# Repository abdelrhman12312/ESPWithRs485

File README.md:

# ESPWithRs485
it's a master board that controls multiple slave ones with the esp-12e 
you can use this link to view the pcb in your browser 
https://kicanvas.org/?github=https%3A%2F%2Fgithub.com%2Fabdelrhman12312%2FESPWithRs485

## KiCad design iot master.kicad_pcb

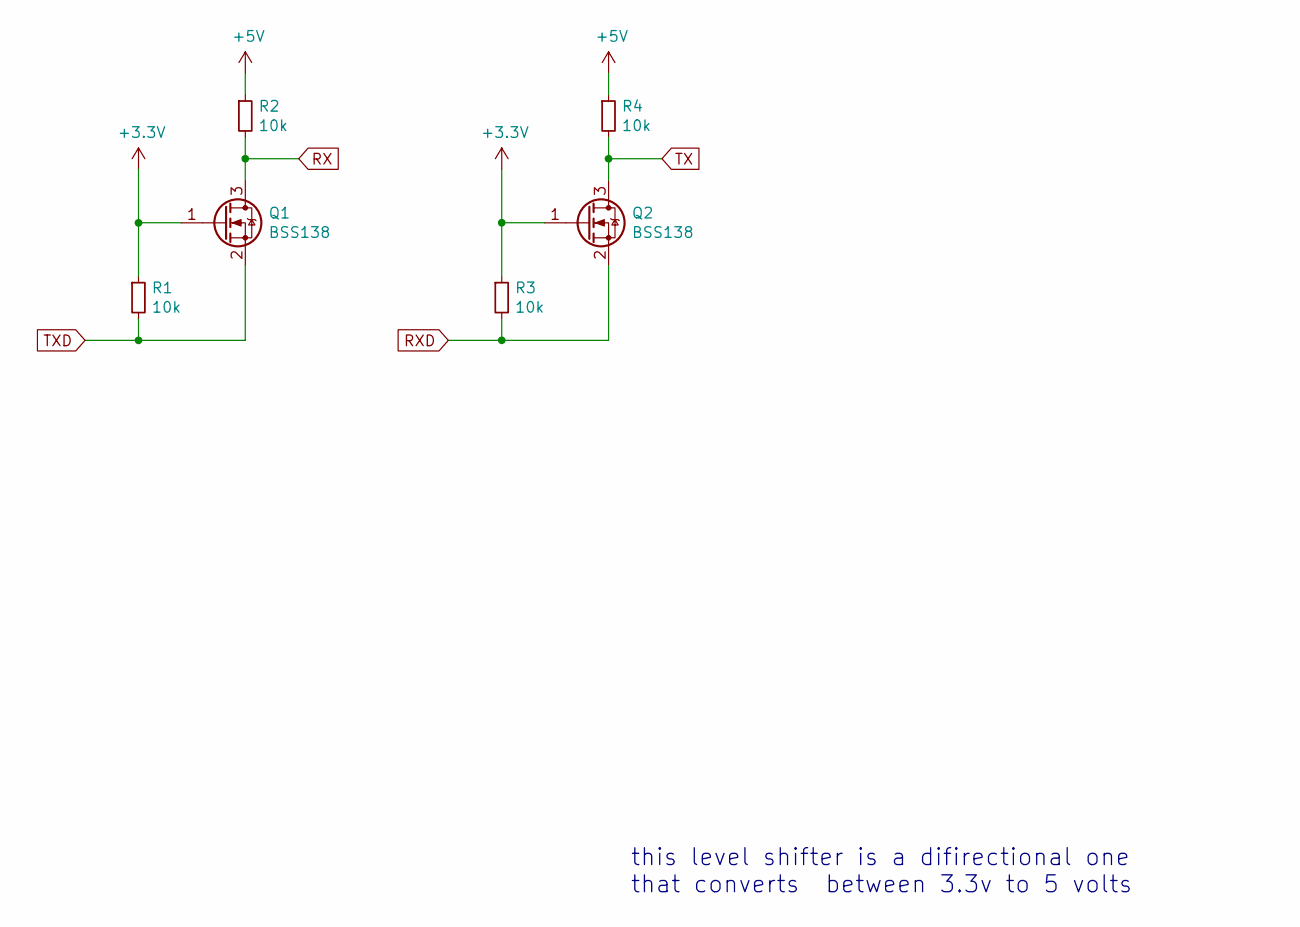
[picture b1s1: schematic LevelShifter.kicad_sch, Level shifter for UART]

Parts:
Q1, Q2: BSS138; SOT-23
R1, R2, R3, R4: 10k; R_0805_2012Metric_Pad1.15x1.40mm_HandSolder

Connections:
+3V3: Q1.1 (G), Q2.1 (G), R1.1, R3.1; also elsewhere on the board
+5V: R2.1, R4.1; also elsewhere on the board
RX: Q1.3 (D), R2.2; also elsewhere on the board
RXD: Q2.2 (S), R3.2; also elsewhere on the board
TX: Q2.3 (D), R4.2; also elsewhere on the board
TXD: Q1.2 (S), R1.2; also elsewhere on the board

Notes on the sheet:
this level shifter is a difirectional one that converts between 3.3v to 5 volts

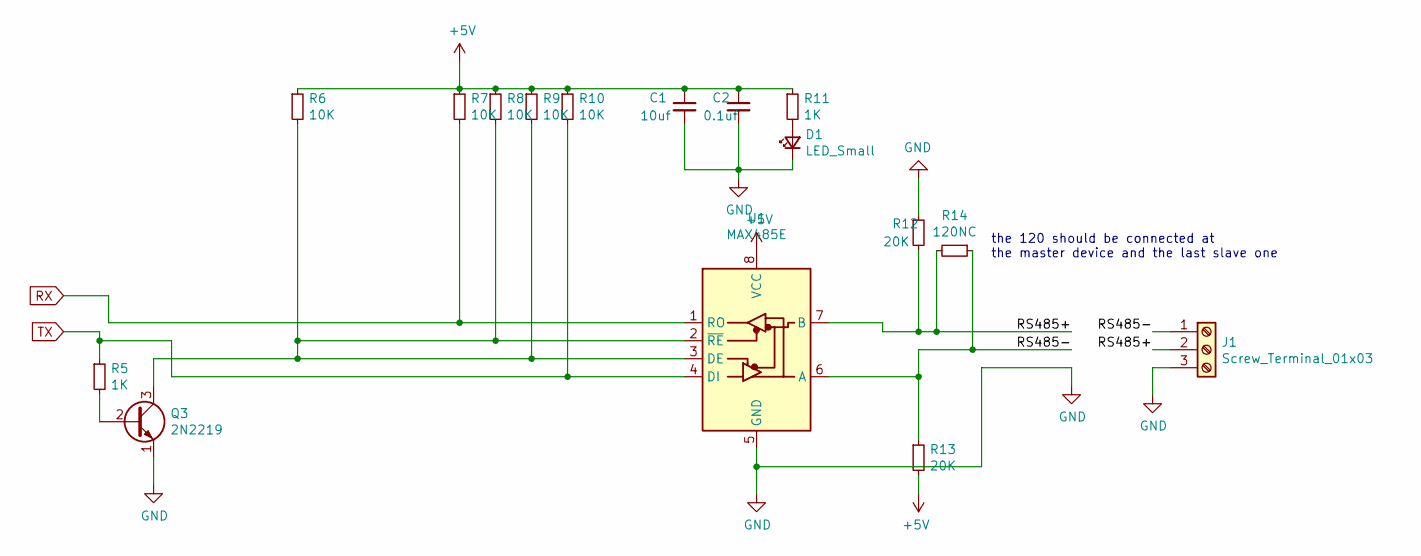
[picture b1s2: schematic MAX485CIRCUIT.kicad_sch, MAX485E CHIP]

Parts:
C1: 10uf; C_0805_2012Metric_Pad1.15x1.40mm_HandSolder
C2: 0.1uf; C_0805_2012Metric_Pad1.15x1.40mm_HandSolder
D1: LED_Small; LED_1206_3216Metric_Pad1.42x1.75mm_HandSolder
J1: Screw_Terminal_01x03; TerminalBlock_bornier-3_P5.08mm
Q3: 2N2219; TO-39-3
R5, R11: 1K; R_0805_2012Metric_Pad1.15x1.40mm_HandSolder
R6, R7, R8, R9, R10: 10K; R_0805_2012Metric_Pad1.15x1.40mm_HandSolder
R12, R13: 20K; R_0805_2012Metric_Pad1.15x1.40mm_HandSolder
R14: 120NC; R_0805_2012Metric_Pad1.15x1.40mm_HandSolder
U1: MAX485E; DIP-8_W7.62mm

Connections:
+5V: C1.1, C2.1, R6.1, R7.1, R8.1, R9.1, R10.1, R11.1, R13.2, U1.8 (VCC); also elsewhere on the board
/MAX485CIRCUIT/RS485+: J1.2, R12.2, R14.2, U1.7 (B)
/MAX485CIRCUIT/RS485-: J1.1, R13.1, R14.1, U1.6 (A)
GND: C1.2, C2.2, D1.1 (K), J1.3, Q3.1 (E), R12.1, U1.5 (GND); also elsewhere on the board
unnamed: D1.2 (A), R11.2
unnamed: Q3.2 (B), R5.2
unnamed: Q3.3 (C), R6.2, R8.2, R9.2, U1.2 (~RE), U1.3 (DE)
RX: R7.2, U1.1 (RO); also elsewhere on the board
TX: R5.1, R10.2, U1.4 (DI); also elsewhere on the board

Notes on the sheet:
the 120 should be connected at the master device and the last slave one

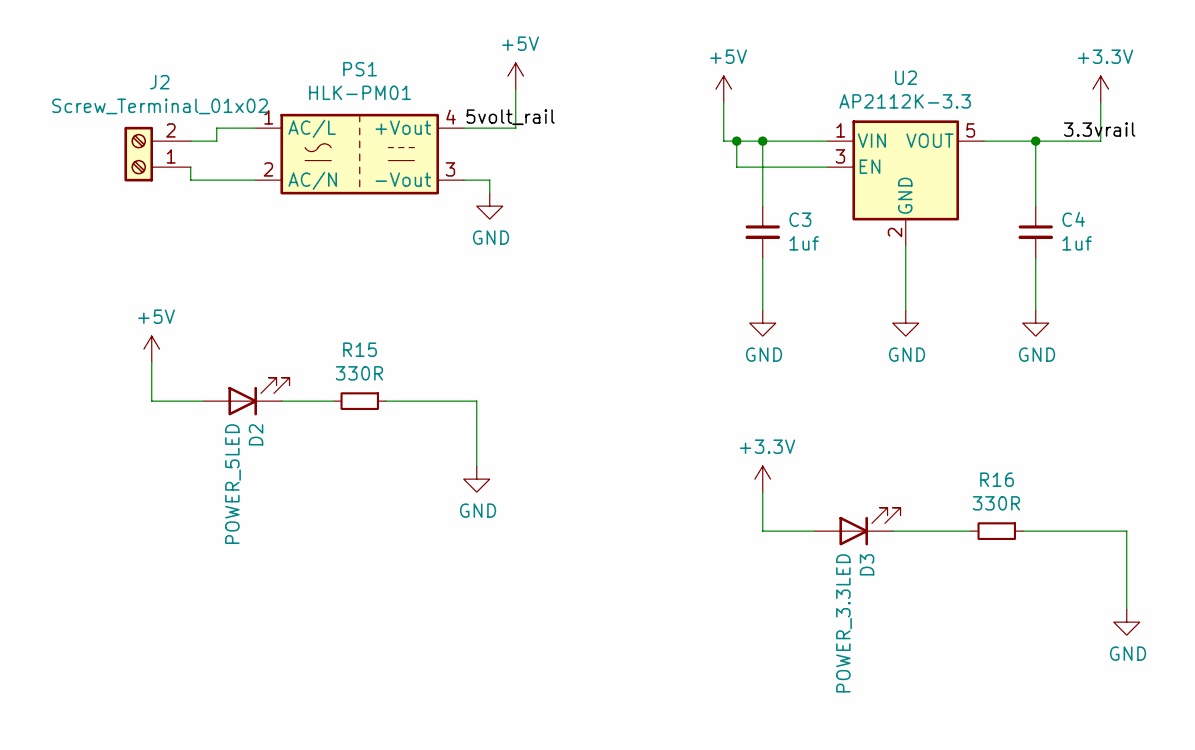
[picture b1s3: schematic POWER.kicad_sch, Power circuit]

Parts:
C3, C4: 1uf; R_0805_2012Metric_Pad1.15x1.40mm_HandSolder
D2: POWER_5LED; LED_1206_3216Metric_Pad1.42x1.75mm_HandSolder
D3: POWER_3.3LED; LED_1206_3216Metric_Pad1.42x1.75mm_HandSolder
J2: Screw_Terminal_01x02; TerminalBlock_bornier-2_P5.08mm
PS1: HLK-PM01; Converter_ACDC_HiLink_HLK-PMxx
R15, R16: 330R; R_0805_2012Metric_Pad1.15x1.40mm_HandSolder
U2: AP2112K-3.3; SOT-23-5

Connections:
+3V3: C4.1, D3.2 (A), U2.5 (VOUT); also elsewhere on the board
+5V: C3.1, D2.2 (A), PS1.4 (+Vout), U2.1 (VIN), U2.3 (EN); also elsewhere on the board
GND: C3.2, C4.2, PS1.3 (-Vout), R15.1, R16.1, U2.2 (GND); also elsewhere on the board
unnamed: D2.1 (K), R15.2
unnamed: D3.1 (K), R16.2
unnamed: J2.1, PS1.2 (AC/N)
unnamed: J2.2, PS1.1 (AC/L)

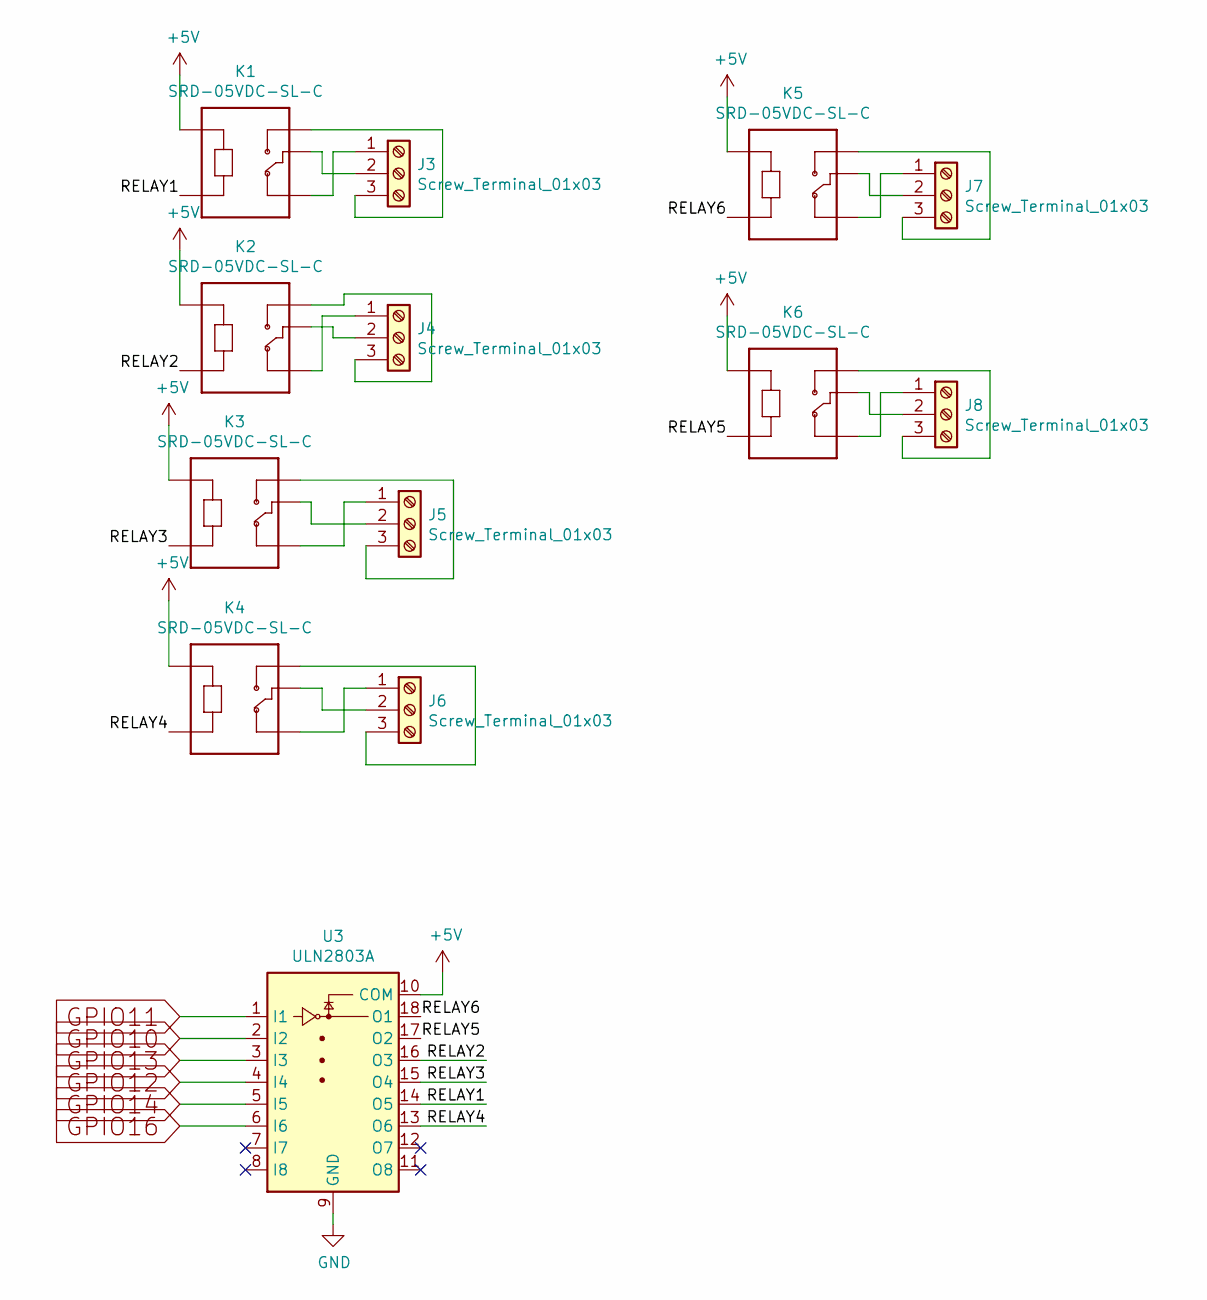
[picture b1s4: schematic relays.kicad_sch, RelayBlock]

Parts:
J3, J4, J5, J6, J7, J8: Screw_Terminal_01x03; TerminalBlock_bornier-3_P5.08mm
K1, K2, K3, K4, K5, K6: SRD-05VDC-SL-C; RELAY_SRD-05VDC-SL-C
U3: ULN2803A; SOIC-18W_7.5x11.6mm_P1.27mm

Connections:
+5V: K1.A1, K2.A1, K3.A1, K4.A1, K5.A1, K6.A1, U3.10 (COM); also elsewhere on the board
/relays/RELAY1: K1.A2, U3.14 (O5)
/relays/RELAY2: K2.A2, U3.16 (O3)
/relays/RELAY3: K3.A2, U3.15 (O4)
/relays/RELAY4: K4.A2, U3.13 (O6)
/relays/RELAY5: K6.A2, U3.17 (O2)
/relays/RELAY6: K5.A2, U3.18 (O1)
GND: U3.9 (GND); also elsewhere on the board
GPIO10: U3.2 (I2); also elsewhere on the board
GPIO11: U3.1 (I1); also elsewhere on the board
GPIO12: U3.4 (I4); also elsewhere on the board
GPIO13: U3.3 (I3); also elsewhere on the board
GPIO14: U3.5 (I5); also elsewhere on the board
GPIO16: U3.6 (I6); also elsewhere on the board
unnamed: J3.1, K1.NC
unnamed: J3.2, K1.COM
unnamed: J3.3, K1.NO
unnamed: J4.1, K2.NC
unnamed: J4.2, K2.COM
unnamed: J4.3, K2.NO
unnamed: J5.1, K3.NC
unnamed: J5.2, K3.COM
unnamed: J5.3, K3.NO
unnamed: J6.1, K4.NC
unnamed: J6.2, K4.COM
unnamed: J6.3, K4.NO
unnamed: J7.1, K5.NC
unnamed: J7.2, K5.COM
unnamed: J7.3, K5.NO
unnamed: J8.1, K6.NC
unnamed: J8.2, K6.COM
unnamed: J8.3, K6.NO

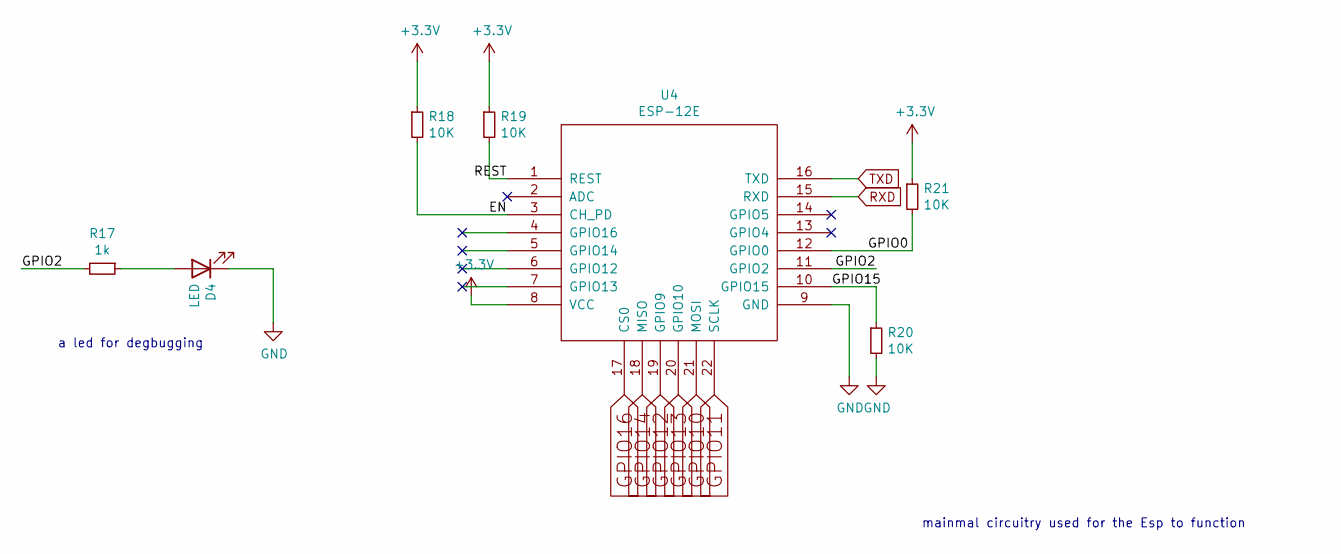
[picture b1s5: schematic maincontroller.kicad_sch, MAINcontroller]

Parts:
D4: LED; LED_1206_3216Metric_Pad1.42x1.75mm_HandSolder
R17: 1k; R_0805_2012Metric_Pad1.15x1.40mm_HandSolder
R18, R19, R20, R21: 10K; R_0805_2012Metric_Pad1.15x1.40mm_HandSolder
U4: ESP-12E

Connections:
+3V3: R18.1, R19.1, R21.1, U4.8 (VCC); also elsewhere on the board
/maincontroller/EN: R18.2, U4.3 (CH_PD)
/maincontroller/GPIO0: R21.2, U4.12 (GPIO0); also elsewhere on the board
/maincontroller/GPIO2: R17.2, U4.11 (GPIO2)
/maincontroller/GPIO15: R20.1, U4.10 (GPIO15)
/maincontroller/REST: R19.2, U4.1 (REST); also elsewhere on the board
GND: D4.1 (K), R20.2, U4.9 (GND); also elsewhere on the board
GPIO10: U4.21 (MOSI); also elsewhere on the board
GPIO11: U4.22 (SCLK); also elsewhere on the board
GPIO12: U4.19 (GPIO9); also elsewhere on the board
GPIO13: U4.20 (GPIO10); also elsewhere on the board
GPIO14: U4.18 (MISO); also elsewhere on the board
GPIO16: U4.17 (CS0); also elsewhere on the board
unnamed: D4.2 (A), R17.1
RXD: U4.15 (RXD); also elsewhere on the board
TXD: U4.16 (TXD); also elsewhere on the board

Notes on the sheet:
a led for degbugging
mainmal circuitry used for the Esp to function

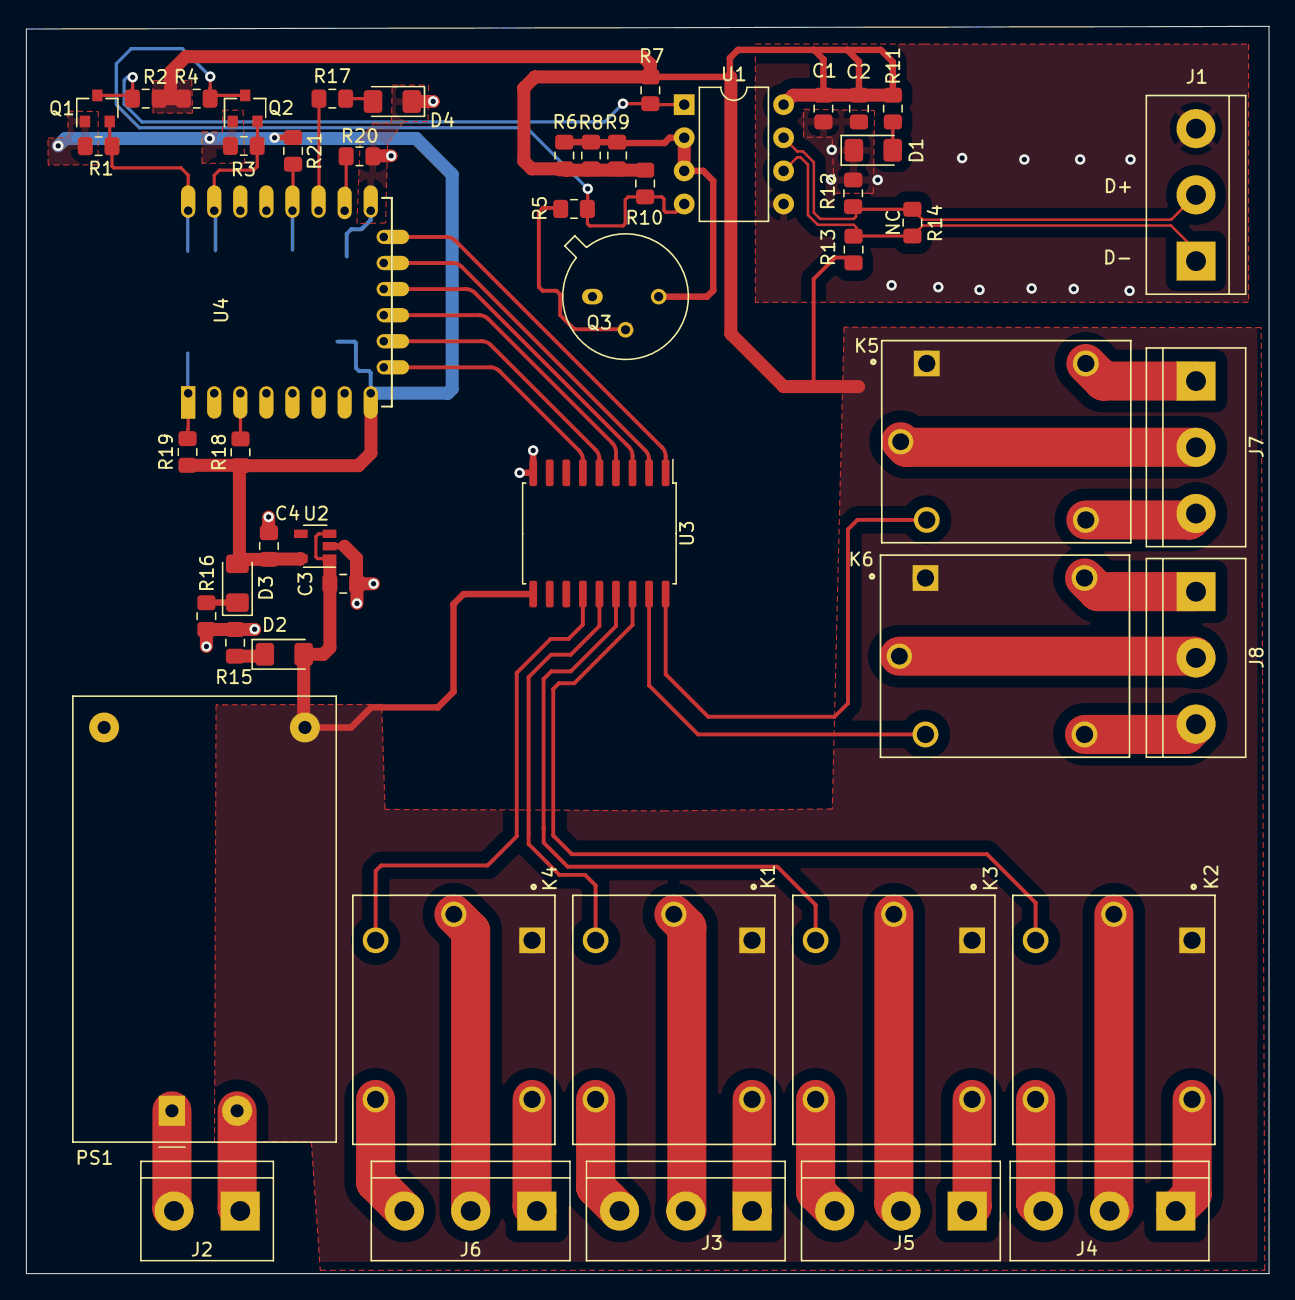
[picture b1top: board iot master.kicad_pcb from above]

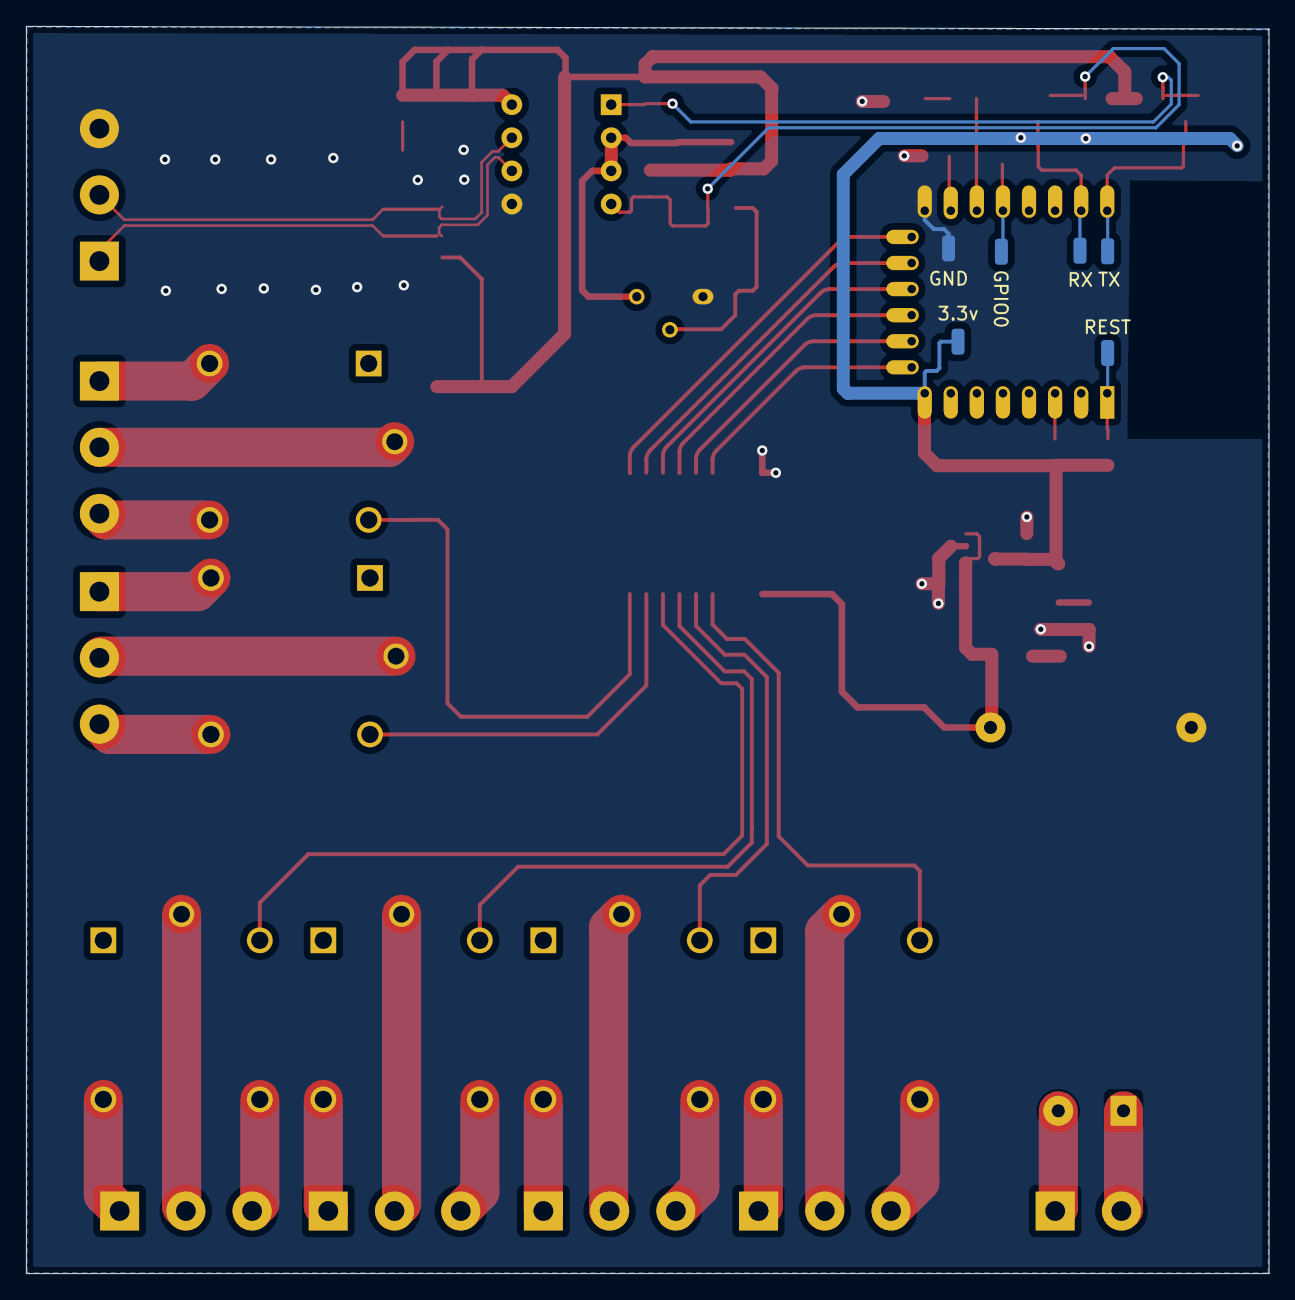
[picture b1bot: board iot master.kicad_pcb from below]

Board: 2 copper layers, 95.3 x 95.7 mm, 57 parts (6 on the bottom side), 52 nets.

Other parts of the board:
3.3v: SolderWirePad_1x01_SMD_1x2mm
GND: SolderWirePad_1x01_SMD_1x2mm
GPIO0: SolderWirePad_1x01_SMD_1x2mm
REST: SolderWirePad_1x01_SMD_1x2mm
RX: SolderWirePad_1x01_SMD_1x2mm
TX: SolderWirePad_1x01_SMD_1x2mm

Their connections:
+3V3: 3.3v.1; also elsewhere on the board
/maincontroller/GPIO0: GPIO0.1; also elsewhere on the board
/maincontroller/REST: REST.1; also elsewhere on the board
RXD: RX.1; also elsewhere on the board
TXD: TX.1; also elsewhere on the board

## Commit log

2022-09-27 Create png
2022-10-05 Create pics
